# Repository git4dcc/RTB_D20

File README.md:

# RTB_D20

My Homebrew [D20](https://rtb4dcc.de/hardware/decoder/d20/) decoder is a double sided mobile decoder with NEM-651 connector. The decoder is designed to integrate into the [RTB](https://rtb4dcc.de/concept/) digital control infrastructure.

<details>
<summary>See also</summary>

- [RTB_D12 - custom](/../../../../git4dcc/RTB_D12) (Fleischmann V100)
- [RTB_D13 - custom](/../../../../git4dcc/RTB_D13) (Minitrix coach)
- [RTB_D15 - custom](/../../../../git4dcc/RTB_D15) (Minitrix V160)
- [RTB_D16 - NEM651](/../../../../git4dcc/RTB_D16)
- [RTB_D21 - Next18](/../../../../git4dcc/RTB_D21)
- [RTB_D22 - Plux16](/../../../../git4dcc/RTB_D22)
- [RTB_D23 - NEM652](/../../../../git4dcc/RTB_D23)

</details>

<details>
<summary>User Guides</summary>

- User Guide - DE
- [User Guide - EN](https://rtb4dcc.de/rtb_decoder_reference_en/)

</details>

<br>

The decoder has the following features,
- **NEM-651** connector
- **DCC**
  - DCC-A automatic logon
  - DCC-R protocol extension
  - Service Mode Programming
- **Railcom**
  - Channel 1/2
  - POM, xPOM
  - DYN: Speed, QoS, Track-voltage, Motor-current, AUX-current, Temp, Distance travelled
- Double sided
- Dimension: 14 x 8 mm
- 7-20V track voltage
- heartbeat LED
- adjustable max motor current (default 300mA)
- adjustable max AUX current (default 500mA)
- over temp protection
- Function output: LF/LR (dimmable, 1.4kHz) open drain
- Function output: AUX1/AUX2 (dimmable, 1.4kHz) open drain and logic level (3.3V)
- Function output: AUX3/AUX4 logic level (3.3V)
- optional external buffer capacitor (max. 1500uF)
- <10mA idle power consumption
- Firmware update over main tracks via DCC-R protocol

# Hardware
The current PCB layout uses SMD footprints with 0.5mm pitch, 0402 and 0201 parts. Reflow soldering is mandatory.

## PCB
- 6-layer PCB, FR4, 14 x 8 x 0.8mm (double sided)
- CPU: AVR64DD28
- Motor bridge: DRV8231
- Connector: NEM-651

## Kicad
[Schematic](doc/D20_schematic.pdf) | [Layout](doc/D20_layout.pdf) | [Gerber](gerber)

<details>
<summary>Dependency</summary>
<br>

:yellow_circle: Requires my Kicad project library [RTB_SamacSys](https://github.com/git4dcc/RTB_SamacSys) in the same directory tree.

</details>

## Firmware
Filename structure: { **pcb** }{ **code** }{ **version** }.hex

Example: **D20F0001**.hex

|   | Description |
| --- | --- |
| **pcb** | Name of matching hardware (**D20**) |
| **code** | Type of code contained (**R**=rom, **B**=bootloader, **F**=flash, **U**=bld update, **P**=UPDI factory code) |
| **version** | Release version (**####**) |

[Firmware files](firmware)

## UPDI
The fuse settings as well as the P-code (D20Pxxxx.hex) has to be installed by using UPDI.<br>
Connecting the decoder via its track pins to a 5V(DC) power supply will boot its CPU. This way, its easy to program the fuses and flash.

<details>
<summary>Details</summary>

| Fuse Setting | P-code Install |
| --- | --- |
|||

</details>

# Images
| top | bottom |
| --- | --- |
|  |  |

# YouTube
Some YouTubes to see the D20 decoder in action.<br><br>

This project is intended for hobby use only and is distributed in accordance with the Apache License 2.0 agreement.

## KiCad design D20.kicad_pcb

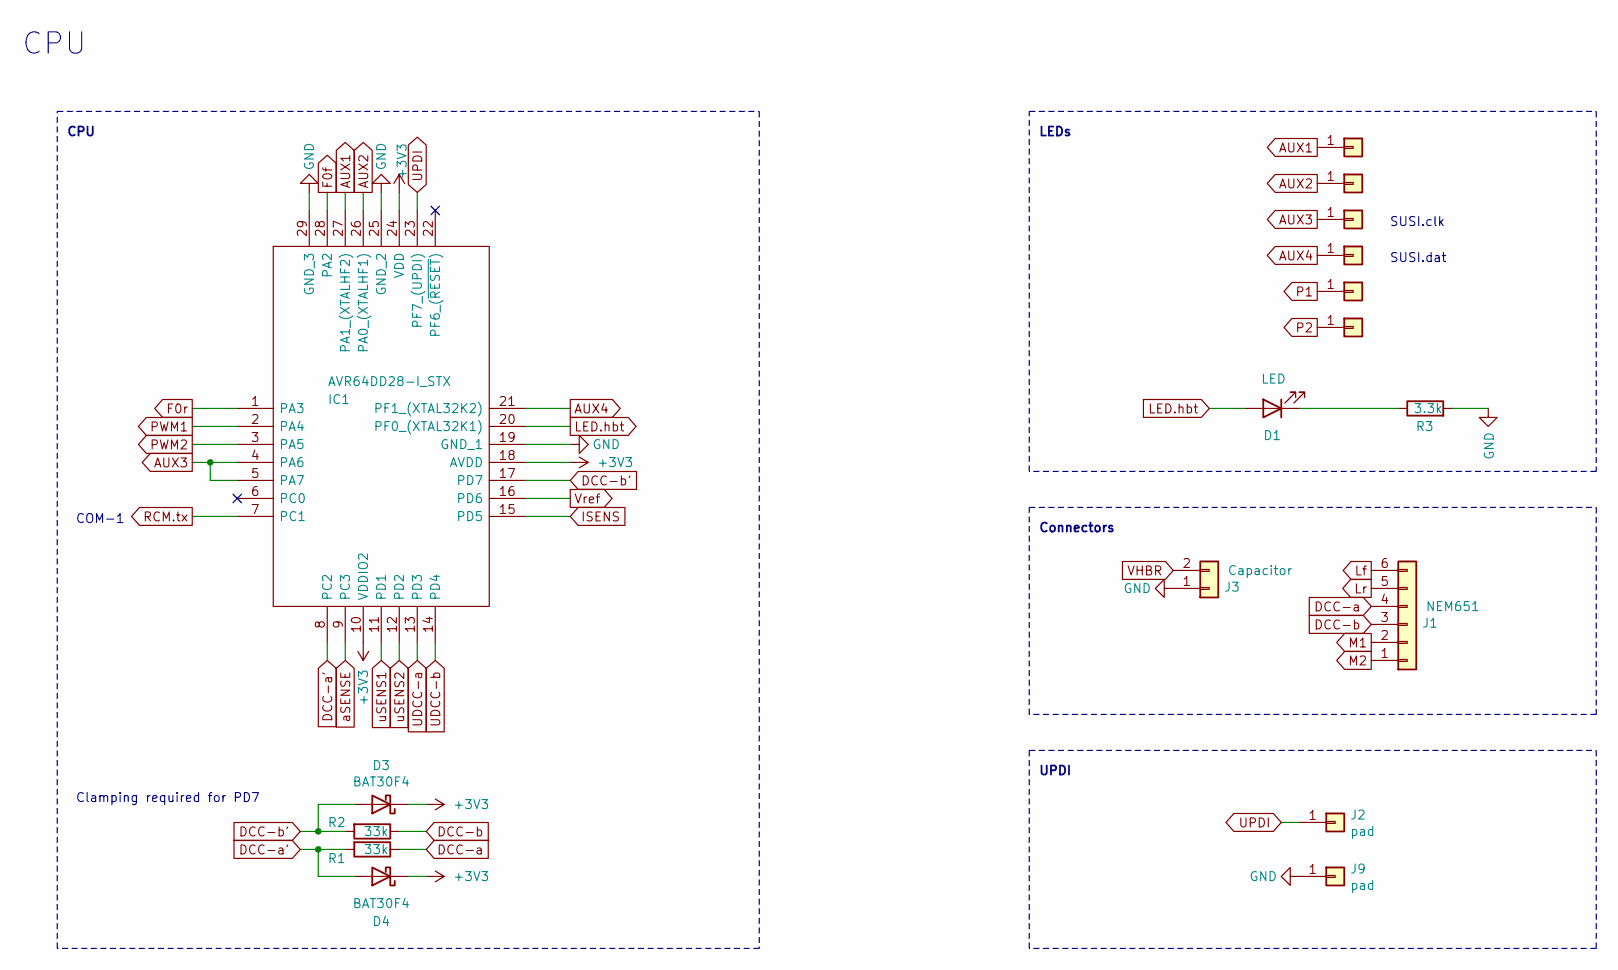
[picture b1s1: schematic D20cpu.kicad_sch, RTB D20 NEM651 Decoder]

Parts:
D1: LED; LED_0402_1005Metric
D3, D4: BAT30F4
IC1: AVR64DD28-I_STX; QFN-28-1EP_4x4mm_P0.4mm_EP2.3x2.3mm; Mouser Part Number 494-AVR64DD28-I/STX
J1: NEM651; PinHeader_1x06_P1.27mm_Horizontal
J2, J9: pad; DummyNet-Connector
J3: Capacitor; PinHeader_1x02_P1.27mm_Horizontal
J4, J5, J6, J7, J8, J10: Conn_01x01; DummyNet-Connector
R1, R2: 33k; R_0402_1005Metric
R3: 3.3k; R_0402_1005Metric

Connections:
+3V3: D3.1 (K), D4.1 (K), IC1.10 (VDDIO2), IC1.18 (AVDD), IC1.24 (VDD); also elsewhere on the board
AUX1: IC1.27 (PA1_(XTALHF2)), J4.1 (Pin_1_1); also elsewhere on the board
AUX2: IC1.26 (PA0_(XTALHF1)), J5.1 (Pin_1_1); also elsewhere on the board
AUX3: IC1.4 (PA6), IC1.5 (PA7), J8.1 (Pin_1_1)
AUX4: IC1.21 (PF1_(XTAL32K2)), J10.1 (Pin_1_1)
DCC-a: J1.4, R1.1; also elsewhere on the board
DCC-a': D4.2 (A), IC1.8 (PC2), R1.2
DCC-b: J1.3, R2.1; also elsewhere on the board
DCC-b': D3.2 (A), IC1.17 (PD7), R2.2
F0f: IC1.28 (PA2); also elsewhere on the board
F0r: IC1.1 (PA3); also elsewhere on the board
GND: IC1.19 (GND_1), IC1.25 (GND_2), IC1.29 (GND_3), J3.1, J9.1 (Pin_1_1), R3.2; also elsewhere on the board
ISENS: IC1.15 (PD5); also elsewhere on the board
LED.hbt: D1.2 (A), IC1.20 (PF0_(XTAL32K1))
Lf: J1.6; also elsewhere on the board
Lr: J1.5; also elsewhere on the board
M1: J1.2; also elsewhere on the board
M2: J1.1; also elsewhere on the board
unnamed: D1.1 (K), R3.1
P1: J6.1 (Pin_1_1); also elsewhere on the board
P2: J7.1 (Pin_1_1); also elsewhere on the board
PWM1: IC1.2 (PA4); also elsewhere on the board
PWM2: IC1.3 (PA5); also elsewhere on the board
RCM.tx: IC1.7 (PC1); also elsewhere on the board
UDCC-a: IC1.13 (PD3); also elsewhere on the board
UDCC-b: IC1.14 (PD4); also elsewhere on the board
UPDI: IC1.23 (PF7_(UPDI)), J2.1 (Pin_1_1)
VHBR: J3.2; also elsewhere on the board
Vref: IC1.16 (PD6); also elsewhere on the board
aSENSE: IC1.9 (PC3); also elsewhere on the board
uSENS1: IC1.11 (PD1); also elsewhere on the board
uSENS2: IC1.12 (PD2); also elsewhere on the board

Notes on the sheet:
SUSI.clk
LEDs
Clamping required for PD7
CPU
UPDI
SUSI.dat
COM-1
Connectors

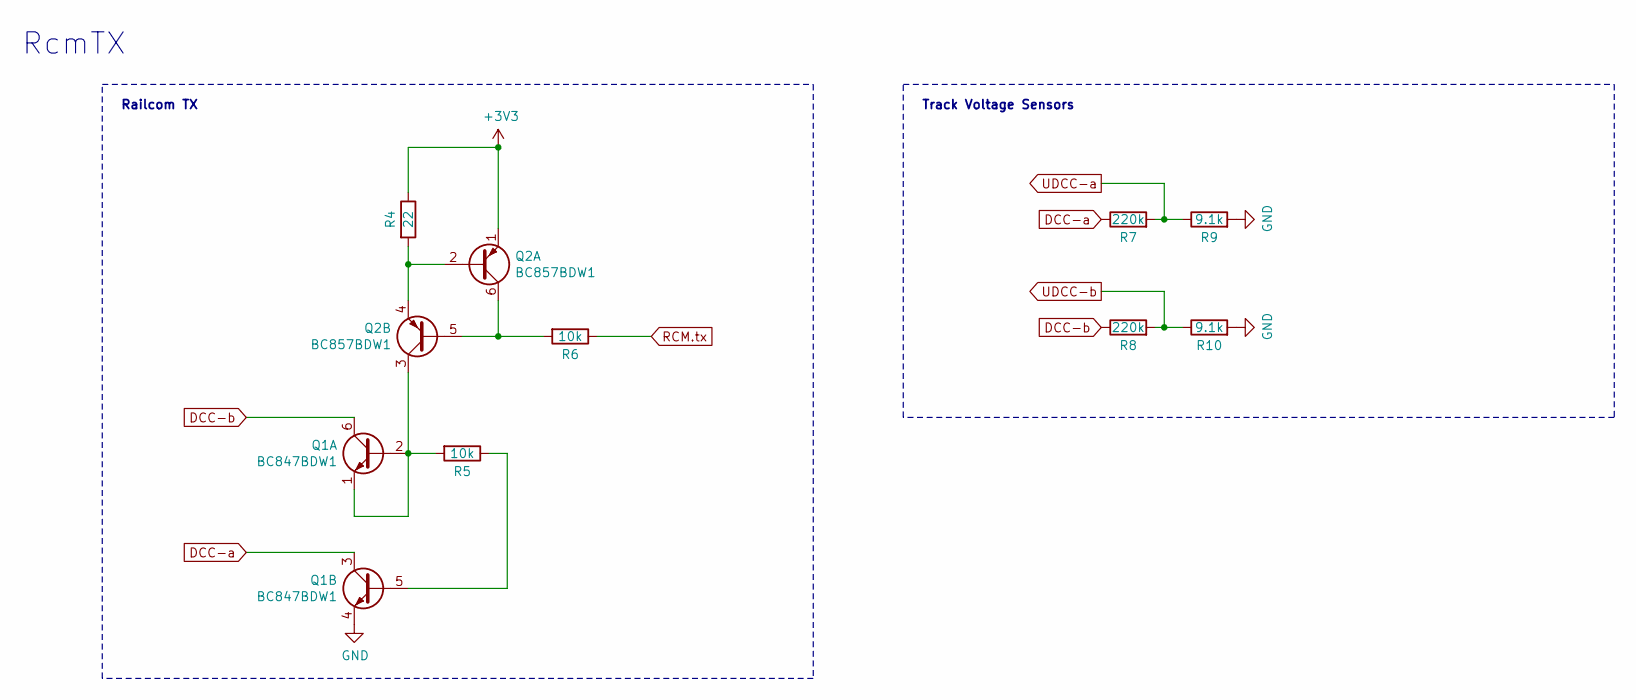
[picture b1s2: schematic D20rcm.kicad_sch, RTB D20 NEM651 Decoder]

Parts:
Q1: BC847BDW1; SOT-666
Q2: BC857BDW1; SOT-666
R4: 22; R_0402_1005Metric
R5, R6: 10k; R_0402_1005Metric
R7, R8: 220k; R_0402_1005Metric
R9, R10: 9.1k; R_0402_1005Metric

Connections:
+3V3: Q2.1 (E1), R4.1; also elsewhere on the board
DCC-a: Q1.3 (C2), R7.1; also elsewhere on the board
DCC-b: Q1.6 (C1), R8.1; also elsewhere on the board
GND: Q1.4 (E2), R9.2, R10.2; also elsewhere on the board
unnamed: Q1.1 (E1), Q1.2 (B1), Q2.3 (C2), R5.2
unnamed: Q1.5 (B2), R5.1
unnamed: Q2.2 (B1), Q2.4 (E2), R4.2
unnamed: Q2.5 (B2), Q2.6 (C1), R6.2
RCM.tx: R6.1; also elsewhere on the board
UDCC-a: R7.2, R9.1; also elsewhere on the board
UDCC-b: R8.2, R10.1; also elsewhere on the board

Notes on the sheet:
Track Voltage Sensors
RcmTX
Railcom TX

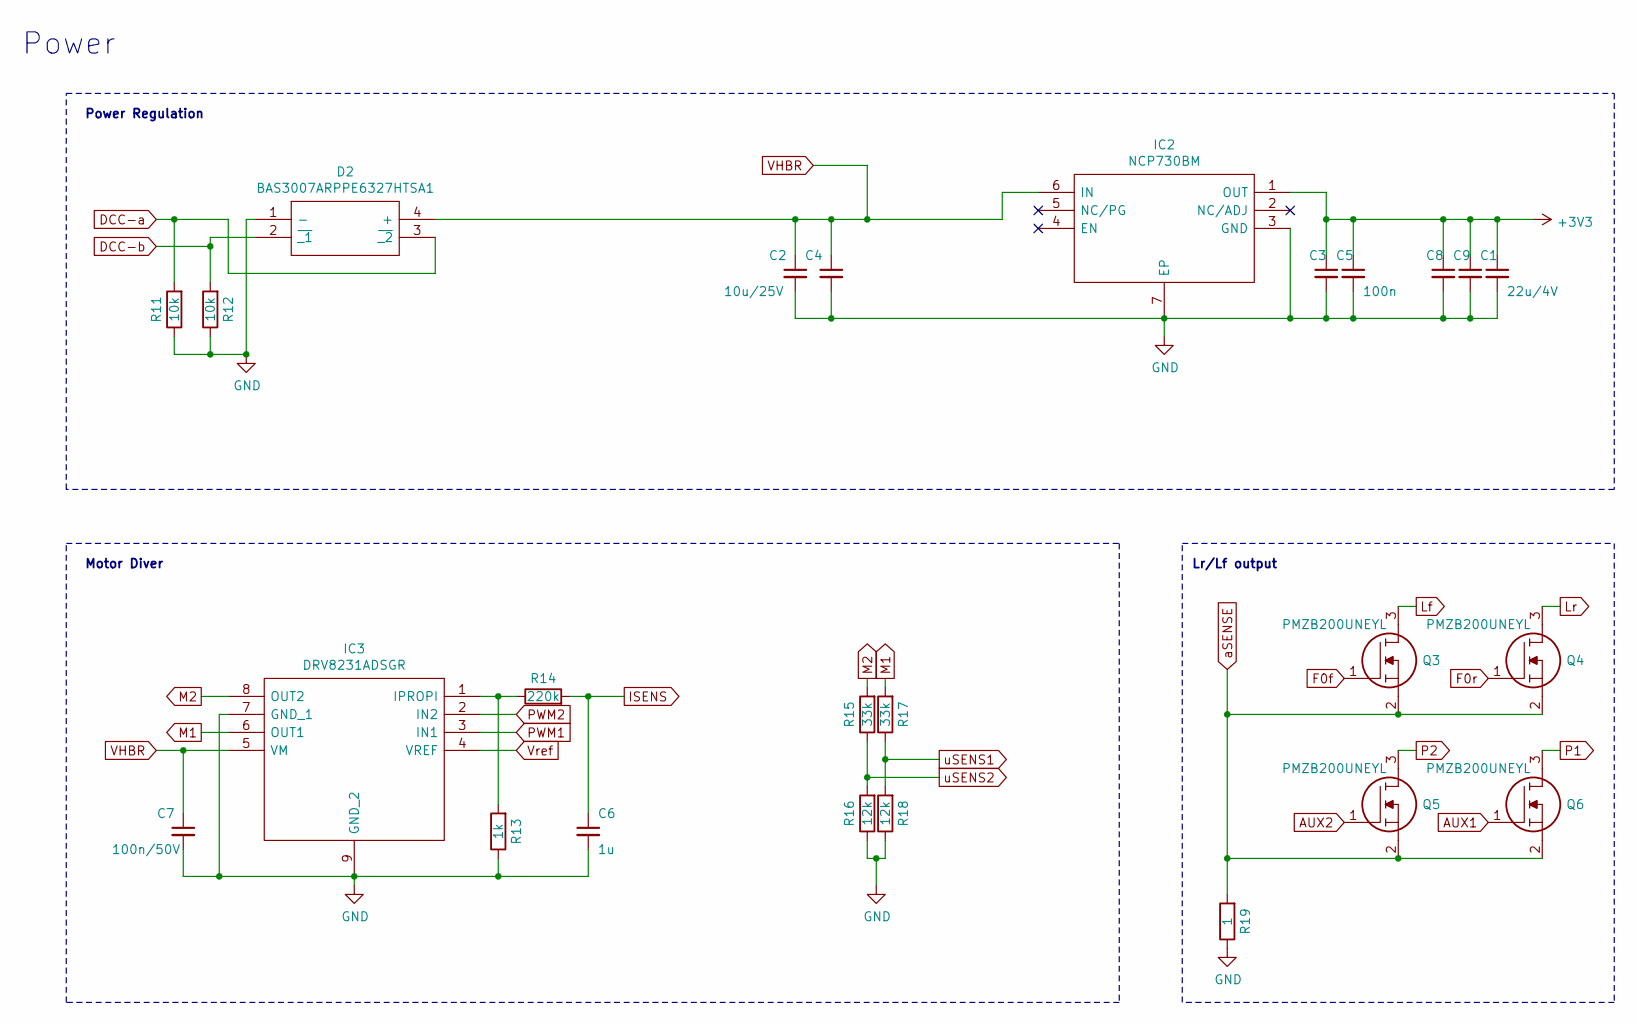
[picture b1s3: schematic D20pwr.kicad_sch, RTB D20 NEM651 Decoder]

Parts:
C1: 22u/4V; C_0402_1005Metric
C2: 10u/25V; C_0603_1608Metric
C3, C5: 100n; C_0402_1005Metric
C4: 22u/25V; C_0603_1608Metric
C6: 1u; C_0402_1005Metric
C7: 100n/50V; C_0603_1608Metric
C8, C9: 22u/6V; C_0402_1005Metric
D2: BAS3007ARPPE6327HTSA1; BF998215; Mouser Part Number 726-BAS3007A-RPPE6
IC2: NCP730BM; WSON-6-1EP_2x2mm_P0.65mm_EP1x1.6mm_ThermalVias; Mouser Part Number 863-NCP730BMT330TBG
IC3: DRV8231ADSGR; SON50P200X200X80-9N; Mouser Part Number 595-DRV8231ADSGR
Q3, Q4, Q5, Q6: PMZB200UNEYL; Diodes_DFN1006-3; LCSC Part # C547292
R11, R12: 10k; R_0402_1005Metric
R13: 1k; R_0402_1005Metric
R14: 220k; R_0402_1005Metric
R15, R17: 33k; R_0402_1005Metric
R16, R18: 12k; R_0402_1005Metric
R19: 1; R_0402_1005Metric

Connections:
+3V3: C1.1, C3.1, C5.1, C8.1, C9.1, IC2.1 (OUT); also elsewhere on the board
AUX1: Q6.1; also elsewhere on the board
AUX2: Q5.1; also elsewhere on the board
DCC-a: D2.3 (~_2), R11.2; also elsewhere on the board
DCC-b: D2.2 (~_1), R12.2; also elsewhere on the board
F0f: Q3.1; also elsewhere on the board
F0r: Q4.1; also elsewhere on the board
GND: C1.2, C2.2, C3.2, C4.2, C5.2, C6.2, C7.2, C8.2, C9.2, D2.1 (-), IC2.3 (GND), IC2.7 (EP), IC3.7 (GND_1), IC3.9 (GND_2), R11.1, R12.1, R13.1, R16.1, R18.1, R19.1; also elsewhere on the board
ISENS: C6.1, R14.2; also elsewhere on the board
Lf: Q3.3; also elsewhere on the board
Lr: Q4.3; also elsewhere on the board
M1: IC3.6 (OUT1), R17.2; also elsewhere on the board
M2: IC3.8 (OUT2), R15.2; also elsewhere on the board
unnamed: IC3.1 (IPROPI), R13.2, R14.1
P1: Q6.3; also elsewhere on the board
P2: Q5.3; also elsewhere on the board
PWM1: IC3.3 (IN1); also elsewhere on the board
PWM2: IC3.2 (IN2); also elsewhere on the board
VHBR: C2.1, C4.1, C7.1, D2.4 (+), IC2.6 (IN), IC3.5 (VM); also elsewhere on the board
Vref: IC3.4 (VREF); also elsewhere on the board
aSENSE: Q3.2, Q4.2, Q5.2, Q6.2, R19.2; also elsewhere on the board
uSENS1: R17.1, R18.2; also elsewhere on the board
uSENS2: R15.1, R16.2; also elsewhere on the board

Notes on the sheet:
Lr/Lf output
Motor Diver
Power Regulation
Power

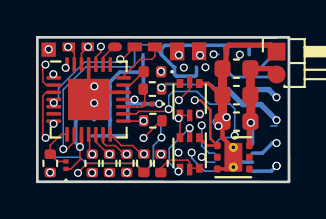
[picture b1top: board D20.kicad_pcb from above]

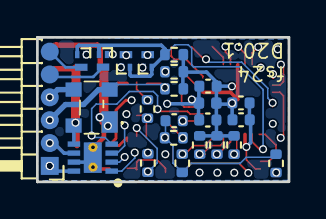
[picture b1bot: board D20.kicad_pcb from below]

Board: 6 copper layers, 14.0 x 8.0 mm, 51 parts (24 on the bottom side), 37 nets.

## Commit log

2024-11-05 initial
2024-11-13 add: clamping diode
2024-11-15 mod: documentation
2025-03-22 add: decoder lock
2025-07-31 add: fuses
2025-07-31 add: updi description
2025-08-05 mod: led automation
2025-10-02 fix: SUSI/AUX
2026-02-20 Update links in README.md to relative paths
2026-02-20 git mirror test
2026-06-26 updated Kicad version

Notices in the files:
D20.kicad_pcb:
Licensed under the Apache License, Version 2
